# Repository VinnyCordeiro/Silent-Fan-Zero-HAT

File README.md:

# Silent Fan Zero HAT
## A PWM to DC voltage conversion in HAT form factor

This board is based on the work of Róbert Lőrincz, from Transylvania, Romania (yes, from the place of Dracula). You can see the original board [here](https://orbiterprojects.com/silent-fan-driver/).

The main purpose of this board is to transform a PWM signal into a DC voltage, with benefits being:
* Lower fan noise;
* Better speed control;
* Longer fan lifetime;
* Lower fan vibrations.

Also, you (theoretically) can control lower voltage fans with this board by setting the maximum fan speed to lower values: using a 24V power supply, you'd use a maximum fan speed of 50% for a 12V fan, and 20% for a 5V fan.

(Photos courtesy of Infinite Entropy, from Voron Discord server)

### UPDATES:

May 4th, 2022: Initial public release (on Star Wars Day! May the Fourth be with you!). I had to reupload many files due to the fact that the pre-release version had messed up silkscreen. 🙃

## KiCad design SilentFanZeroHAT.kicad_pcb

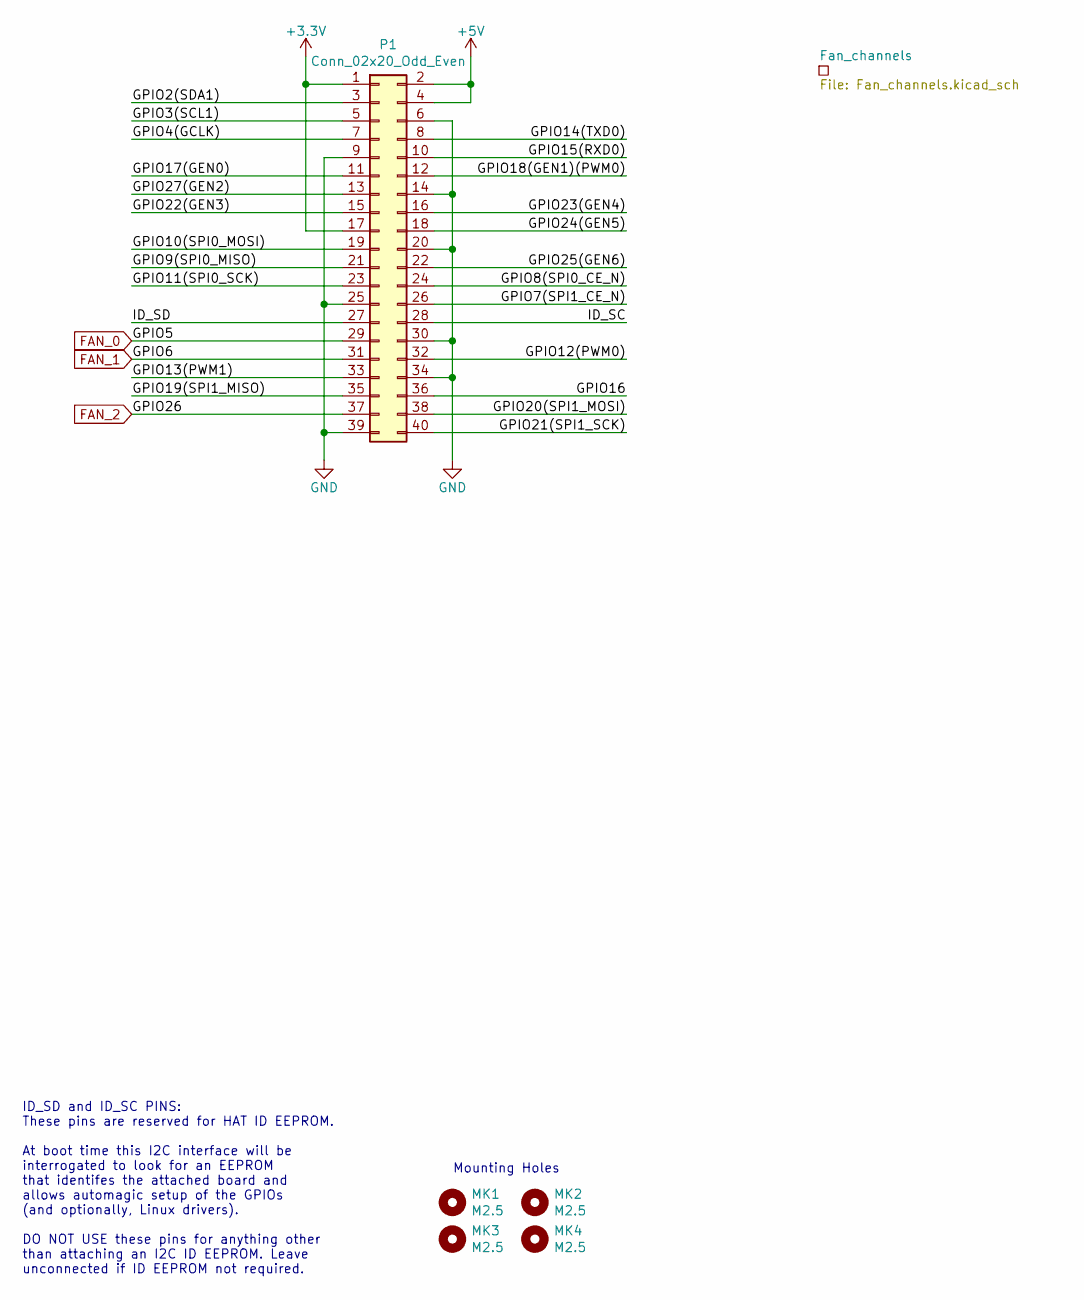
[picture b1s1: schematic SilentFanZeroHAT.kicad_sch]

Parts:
MK1, MK2, MK3, MK4: M2.5; MountingHole_2.7mm_M2.5
P1: Conn_02x20_Odd_Even; PinSocket_2x20_P2.54mm_Vertical

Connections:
+3V3: P1.1, P1.17
+5V: P1.2, P1.4; also elsewhere on the board
/GPIO2(SDA1): P1.3
/GPIO3(SCL1): P1.5
/GPIO4(GCLK): P1.7
/GPIO7(SPI1_CE_N): P1.26
/GPIO8(SPI0_CE_N): P1.24
/GPIO9(SPI0_MISO): P1.21
/GPIO10(SPI0_MOSI): P1.19
/GPIO11(SPI0_SCK): P1.23
/GPIO12(PWM0): P1.32
/GPIO13(PWM1): P1.33
/GPIO14(TXD0): P1.8
/GPIO15(RXD0): P1.10
/GPIO16: P1.36
/GPIO17(GEN0): P1.11
/GPIO18(GEN1)(PWM0): P1.12
/GPIO19(SPI1_MISO): P1.35
/GPIO20(SPI1_MOSI): P1.38
/GPIO21(SPI1_SCK): P1.40
/GPIO22(GEN3): P1.15
/GPIO23(GEN4): P1.16
/GPIO24(GEN5): P1.18
/GPIO25(GEN6): P1.22
/GPIO27(GEN2): P1.13
/ID_SC: P1.28
/ID_SD: P1.27
FAN_0: P1.29; also elsewhere on the board
FAN_1: P1.31; also elsewhere on the board
FAN_2: P1.37; also elsewhere on the board
GND: P1.6, P1.9, P1.14, P1.20, P1.25, P1.30, P1.34, P1.39; also elsewhere on the board

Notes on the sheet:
ID_SD and ID_SC PINS: These pins are reserved for HAT ID EEPROM. At boot time this I2C interface will be interrogated to look for an EEPROM that identifes the attached board and allows automagic setup of the GPIOs (and optionally, Linux drivers). DO NOT USE these pins for anything other than attach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
Mounting Holes

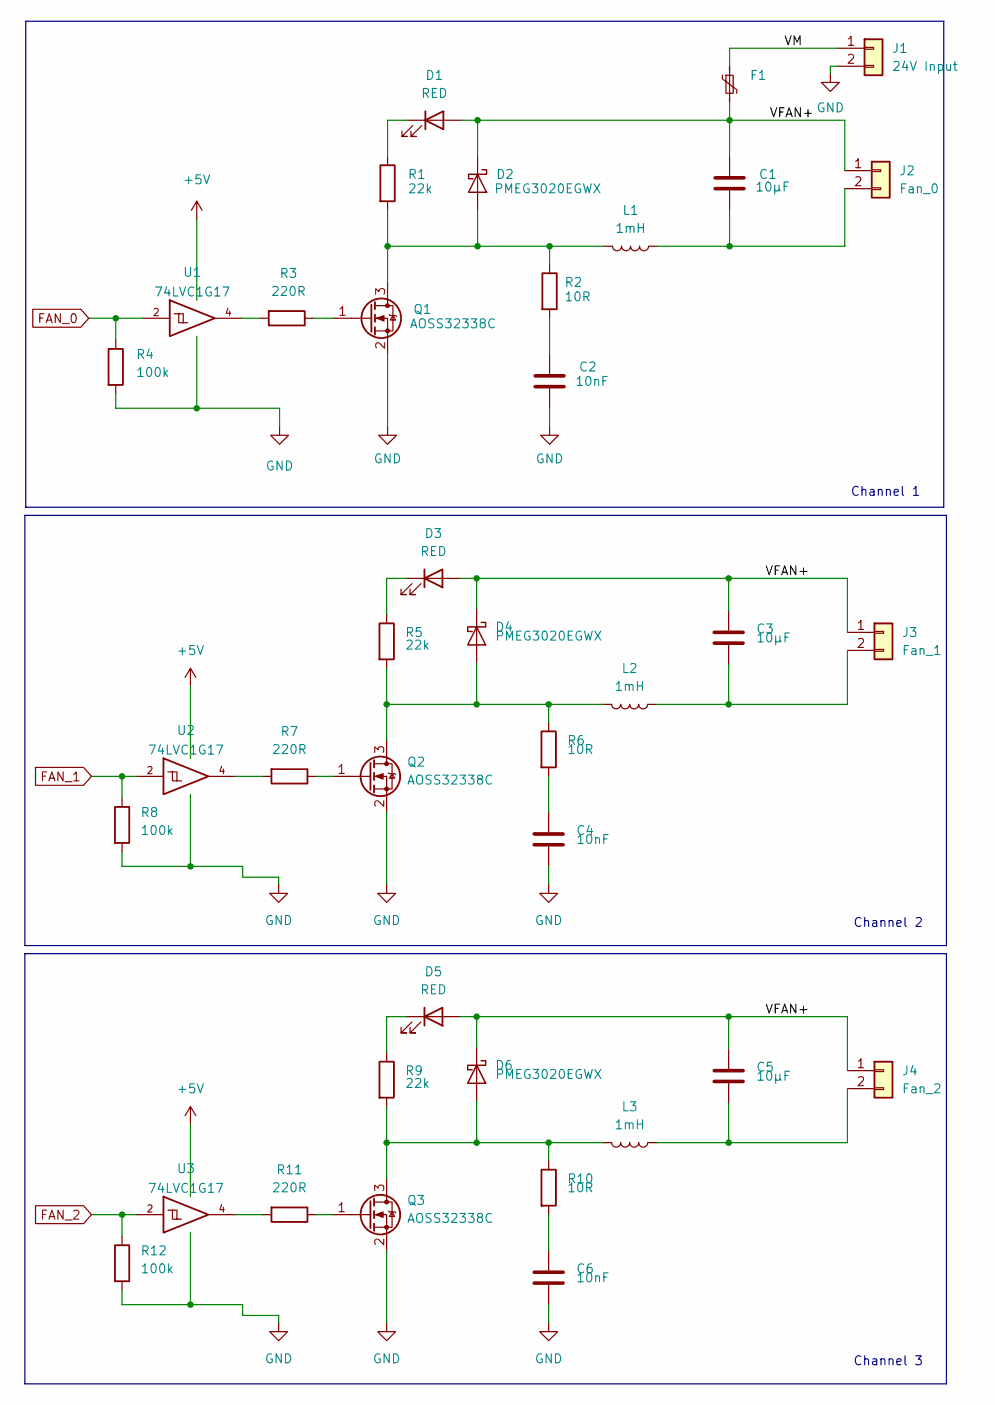
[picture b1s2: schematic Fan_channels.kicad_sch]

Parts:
C1, C3, C5: 10µF; C_1210_3225Metric
C2, C4, C6: 10nF; C_0603_1608Metric
D1, D3, D5: RED; LED_0805_2012Metric
D2, D4, D6: PMEG3020EGWX; D_SOD-123
F1: Fuse_1206_3216Metric
J1: 24V Input; TerminalBlock_Phoenix_MKDS-1,5-2-5.08_1x02_P5.08mm_Horizont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; JLCPCB C91153
J2: Fan_0; JST_XH_B2B-XH-A_1x02_P2.50mm_Vertical
J3: Fan_1; JST_XH_B2B-XH-A_1x02_P2.50mm_Vertical
J4: Fan_2; JST_XH_B2B-XH-A_1x02_P2.50mm_Vertical
L1, L2, L3: 1mH; L_10.4x10.4_H4.8
Q1, Q2, Q3: AOSS32338C; SOT-23
R1, R5, R9: 22k; R_0603_1608Metric
R2, R6, R10: 10R; R_0603_1608Metric
R3, R7, R11: 220R; R_0603_1608Metric
R4, R8, R12: 100k; R_0603_1608Metric
U1, U2, U3: 74LVC1G17; JLCPCB C10425

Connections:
+5V: U1.5 (VCC), U2.5 (VCC), U3.5 (VCC); also elsewhere on the board
/Fan_channels/VFAN+: C1.1, C3.1, C5.1, D1.2 (A), D2.1 (K), D3.2 (A), D4.1 (K), D5.2 (A), D6.1 (K), F1.2, J2.1, J3.1, J4.1
/Fan_channels/VM: F1.1, J1.1
FAN_0: R4.1, U1.2; also elsewhere on the board
FAN_1: R8.1, U2.2; also elsewhere on the board
FAN_2: R12.1, U3.2; also elsewhere on the board
GND: C2.2, C4.2, C6.2, J1.2, Q1.2 (S), Q2.2 (S), Q3.2 (S), R4.2, R8.2, R12.2, U1.3 (GND), U2.3 (GND), U3.3 (GND); also elsewhere on the board
unnamed: C1.2, J2.2, L1.1
unnamed: C2.1, R2.2
unnamed: C3.2, J3.2, L2.1
unnamed: C4.1, R6.2
unnamed: C5.2, J4.2, L3.1
unnamed: C6.1, R10.2
unnamed: D1.1 (K), R1.1
unnamed: D2.2 (A), L1.2, Q1.3 (D), R1.2, R2.1
unnamed: D3.1 (K), R5.1
unnamed: D4.2 (A), L2.2, Q2.3 (D), R5.2, R6.1
unnamed: D5.1 (K), R9.1
unnamed: D6.2 (A), L3.2, Q3.3 (D), R9.2, R10.1
unnamed: Q1.1 (G), R3.1
unnamed: Q2.1 (G), R7.1
unnamed: Q3.1 (G), R11.1
unnamed: R3.2, U1.4
unnamed: R7.2, U2.4
unnamed: R11.2, U3.4

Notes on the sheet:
Channel 2
Channel 1
Channel 3

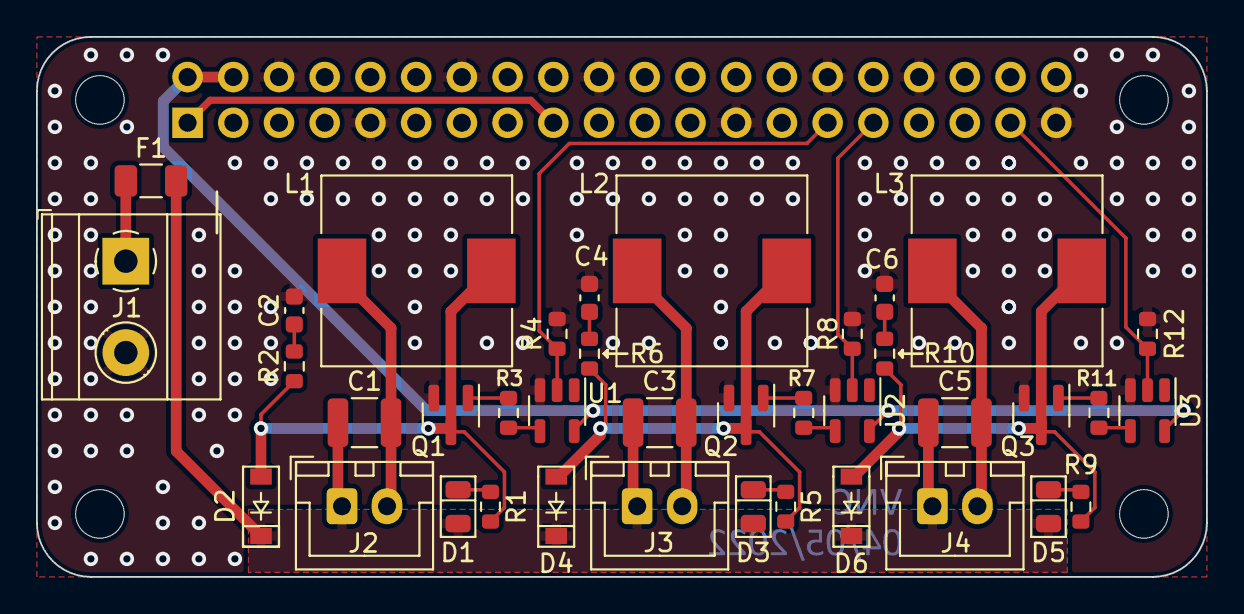
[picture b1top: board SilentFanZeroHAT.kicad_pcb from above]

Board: 2 copper layers, 65.0 x 30.0 mm, 43 parts (1 on the bottom side), 26 nets.

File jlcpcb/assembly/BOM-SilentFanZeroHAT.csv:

Comment,Designator,Footprint,LCSC
Fan_0,"J2,J3,J4",JST_XH_B2B-XH-A_1x02_P2.50mm_Vertical,C158012
74LVC1G17,"U1,U2,U3",SOT-23-5,C202202
10R,"R10,R2,R6",R_0603_1608Metric,C22859
220R,"R11,R3,R7",R_0603_1608Metric,C22962
100k,"R12,R4,R8",R_0603_1608Metric,C25803
22k,"R1,R5,R9",R_0603_1608Metric,C31850
Conn_02x20_Odd_Even,P1,PinSocket_2x20_P2.54mm_Vertical,C35165
10µF,"C1,C3,C5",C_1210_3225Metric,C39232
1mH,"L1,L2,L3",L_10.4x10.4_H4.8,C397811
PMEG3020EGWX,"D2,D4,D6",D_SOD-123,C475720
AOSS32338C,"Q1,Q2,Q3",SOT-23,C489373
10nF,"C2,C4,C6",C_0603_1608Metric,C57112
RED,"D1,D3,D5",LED_0805_2012Metric,C84256
~,F1,Fuse_1206_3216Metric,C910830
24V Input,J1,"TerminalBlock_Phoenix_MKDS-1,5-2-5.08_1x02_P5.08mm_Horizontal",C91153
M2.5,MK1,MountingHole_2.7mm_M2.5,
M2.5,MK3,MountingHole_2.7mm_M2.5,
M2.5,MK2,MountingHole_2.7mm_M2.5,
M2.5,MK4,MountingHole_2.7mm_M2.5,

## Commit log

2022-05-04 Initial upload
2022-05-05 Fixing the silkscreen mess
    Thanks Infinite Entropy for alerting me about that.
2022-05-05 Correcting typo
2022-05-05 Correcting more typos!
2022-05-05 Typo correction: third time is the charm
